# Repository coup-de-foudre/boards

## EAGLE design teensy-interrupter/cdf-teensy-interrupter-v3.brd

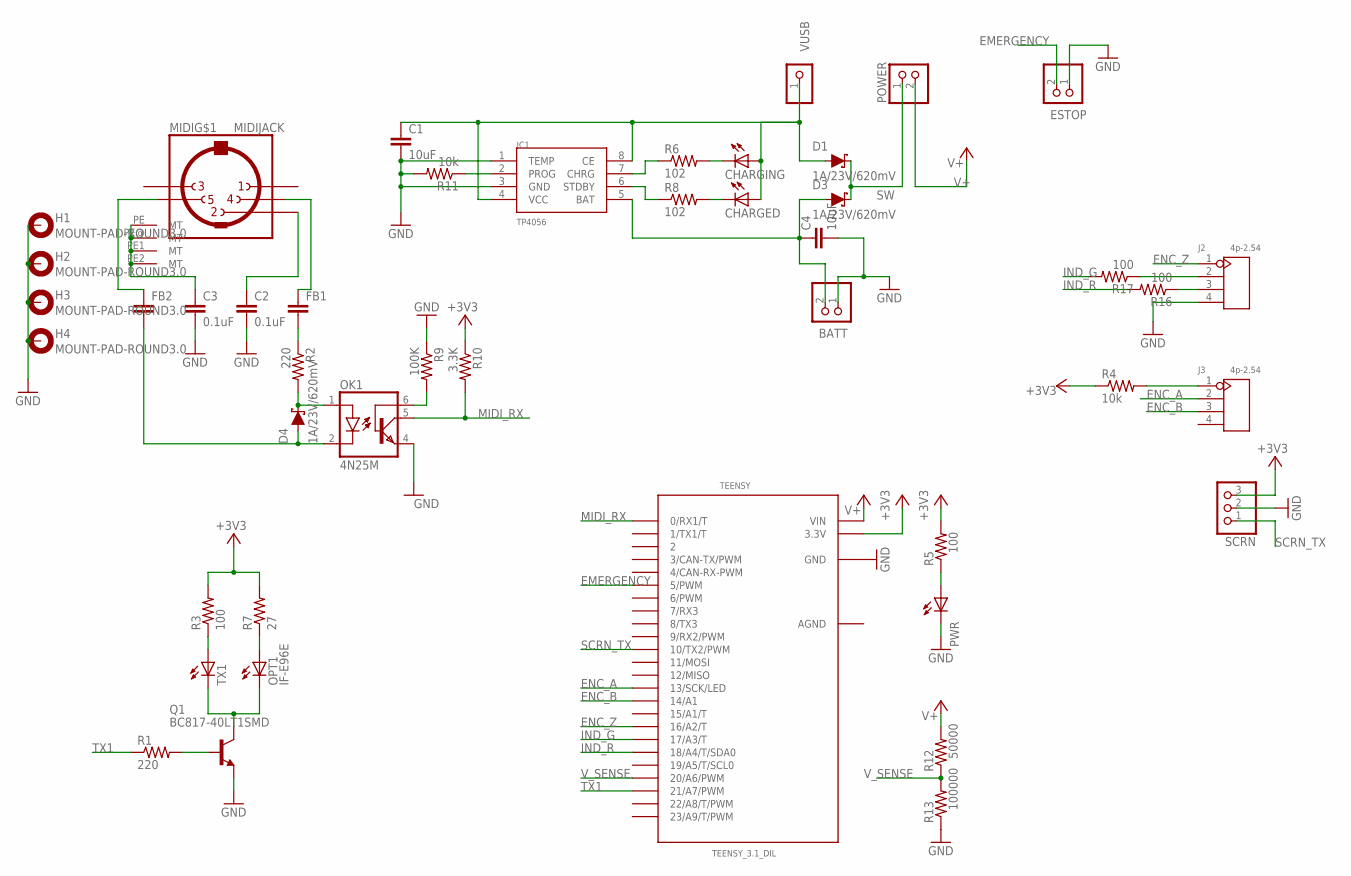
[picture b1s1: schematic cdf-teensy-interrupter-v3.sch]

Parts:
BATT: PINHD-1X2; 1X02
C1, C4: 10uF; C0805
C2, C3: 0.1uF; C0805
CHARGED: LEDCHIP-LED0805; CHIP-LED0805
CHARGING: LEDCHIP-LED0805; CHIP-LED0805
D1, D3, D4: 1A/23V/620mV; SOD-323
ESTOP: PINHD-1X2; 1X02
FB1, FB2: C-EUC0805; C0805
H1, H2, H3, H4: MOUNT-PAD-ROUND3.0; 3,0-PAD
IC1: TP4056; SOP-8
J2, J3: 4p-2.54; H4-2.54
MIDI: MIDIJACK; CP-2350
OK1: 4N25M; DIL06
OPT1: IF-E96E
POWER: PINHD-1X2; 1X02
PWR: LEDCHIP-LED0805; CHIP-LED0805
Q1: BC817-40LT1SMD; SOT23-BEC
R1, R2: 220; R0805
R3, R5, R16, R17: 100; R0805
R4, R11: 10k; R0805
R6, R8: 102; R0805
R7: 27; R0805
R9: 100K; R0805
R10: 3.3K; R0805
R12: 50000; R0805
R13: 100000; R0805
SCRN: PINHD-1X3; 1X03
TEENSY: TEENSY_3.1_DIL; TEENSY3-DIL
TX1: LEDCHIP-LED0805; CHIP-LED0805
VUSB: PINHD-1X1; 1X01

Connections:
+3V3: R3.2, R4.1, R5.2, R7.2, R10.1, SCRN.3, TEENSY.3.3V
AGND: TEENSY.AGND
B+: BATT.2, C4.1, D3.A, IC1.5 (BAT)
EMERGENCY: ESTOP.2, TEENSY.5 (5/PWM)
ENC_A: J3.2, TEENSY.13 (13/SCK/LED)
ENC_B: J3.3, TEENSY.14/A0 (14/A1)
ENC_Z: J2.1, TEENSY.16/A2 (16/A2/T)
GND: BATT.1, C1.2, C2.2, C3.2, C4.2, ESTOP.1, H1.B3,0, H2.B3,0, H3.B3,0, H4.B3,0, IC1.1 (TEMP), IC1.3 (GND), J2.4, OK1.4 (EMI), PWR.C, Q1.E, R9.1, R11.2, R13.1, SCRN.2, TEENSY.GND
IND_G: R17.2, TEENSY.17/A3 (17/A3/T)
IND_R: R16.2, TEENSY.18/A4 (18/A4/T/SDA0)
MIDI_RX: OK1.5 (COL), R10.2, TEENSY.0 (0/RX1/T)
unnamed: FB1.1, MIDI.4
unnamed: D4.C, OK1.1 (A), R2.2
unnamed: D4.A, FB2.2, OK1.2 (C)
unnamed: OK1.6 (BAS), R9.2
unnamed: J3.1, R4.2
unnamed: J2.2, R17.1
unnamed: Q1.B, R1.2
unnamed: OPT1.P$2_ANODE+ (A), R7.1
unnamed: PWR.A, R5.1
unnamed: R3.1, TX1.A
unnamed: OPT1.P$1_CATHODE- (C), Q1.C, TX1.C
unnamed: FB1.2, R2.1
unnamed: C2.1, MIDI.2
unnamed: C3.1, MIDI.PE (MT), MIDI.PE1 (MT), MIDI.PE2 (MT), MIDI.PE@ (MT)
unnamed: FB2.1, MIDI.5
unnamed: IC1.7 (CHRG), R6.1
unnamed: IC1.6 (STDBY), R8.1
unnamed: CHARGED.C, R8.2
unnamed: CHARGING.C, R6.2
unnamed: J2.3, R16.1
unnamed: IC1.2 (PROG), R11.1
SCRN_TX: SCRN.1, TEENSY.10 (10/TX2/PWM)
SW: D1.C, D3.C, POWER.1
TX1: R1.1, TEENSY.21/A7 (21/A7/PWM)
V+: POWER.2, R12.2, TEENSY.VIN
V_SENSE: R12.1, R13.2, TEENSY.20/A6 (20/A6/PWM)
V_USB: C1.1, CHARGED.A, CHARGING.A, D1.A, IC1.4 (VCC), IC1.8 (CE), VUSB.1

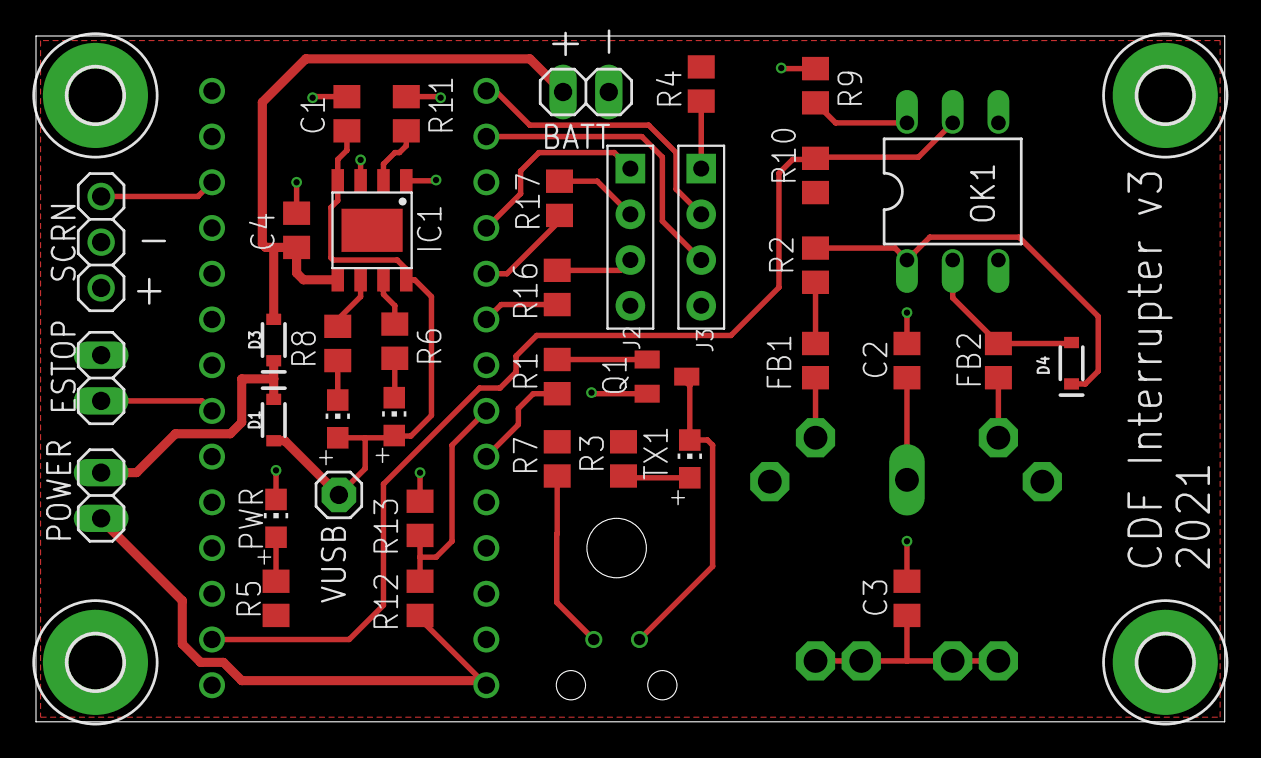
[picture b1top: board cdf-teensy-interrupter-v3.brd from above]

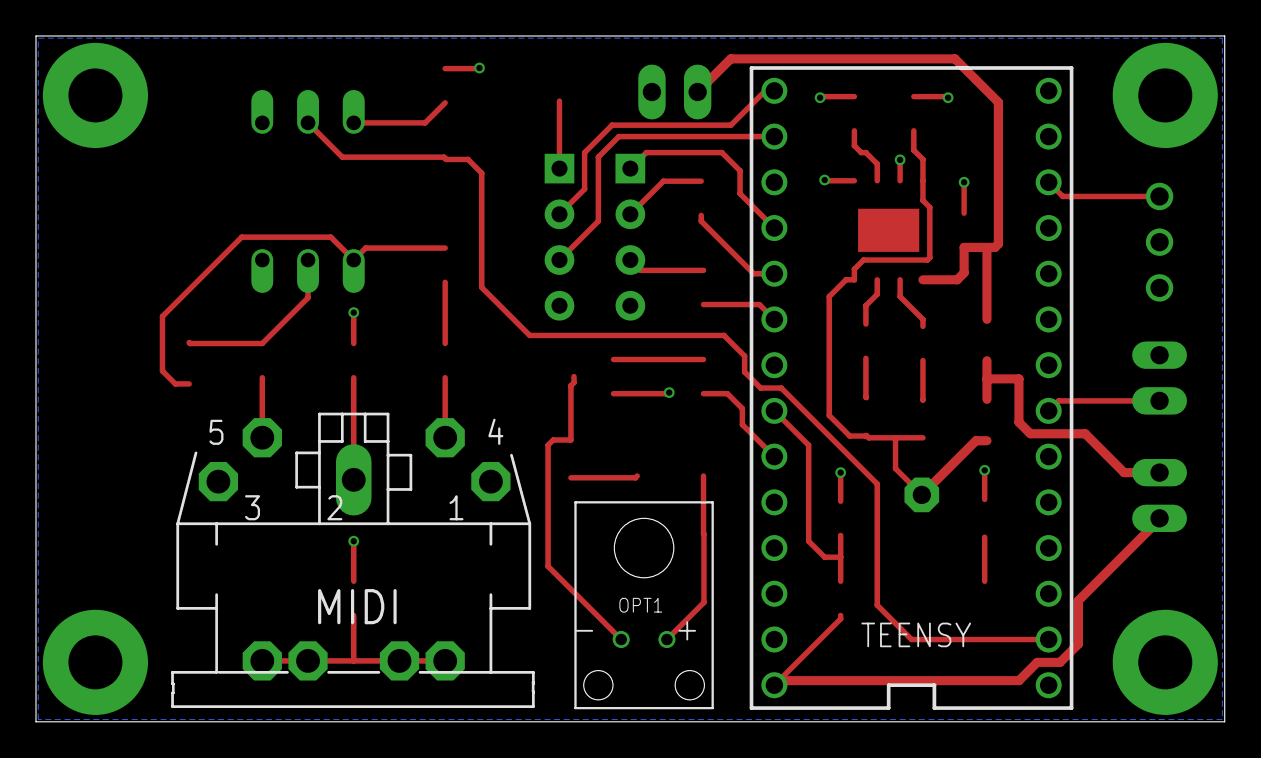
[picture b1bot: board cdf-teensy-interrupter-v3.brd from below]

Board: 2 copper layers, 66.0 x 38.1 mm, 45 parts (3 on the bottom side), 37 nets.

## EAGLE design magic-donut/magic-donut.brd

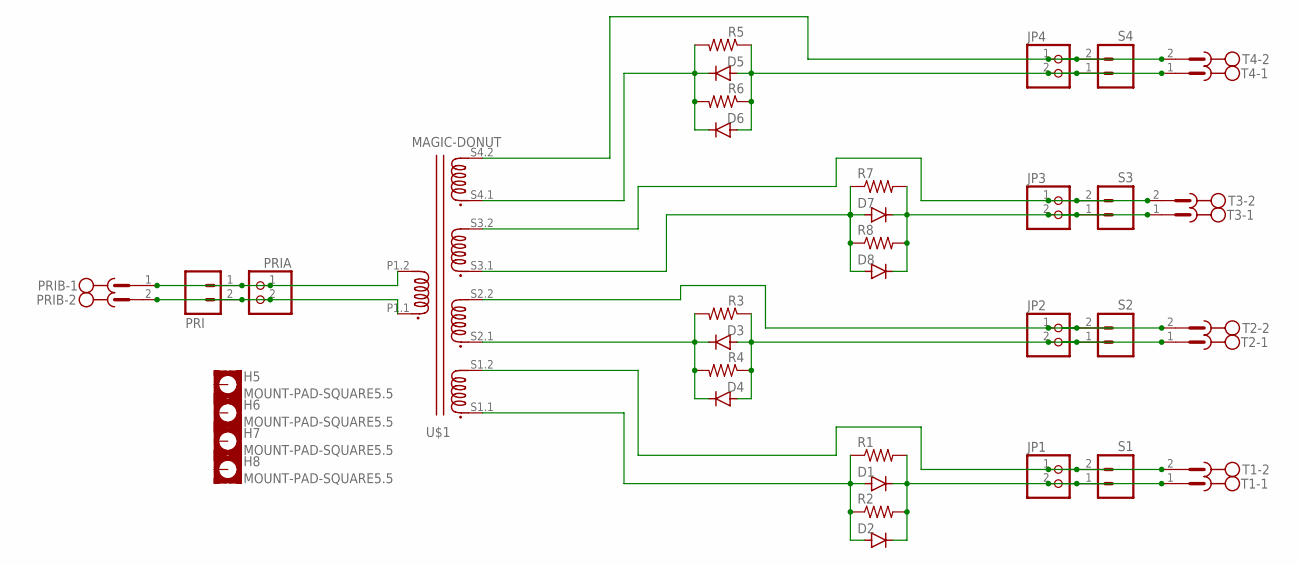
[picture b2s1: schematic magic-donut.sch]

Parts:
D1, D3, D5, D7: DIODE-DO214AA; DO214AA
D2, D4, D6, D8: DIODE-DO201-15; DO201-15
H5, H6, H7, H8: MOUNT-PAD-SQUARE5.5; 5,5-PAD-SQUARE
JP1, JP2, JP3, JP4: PINHD-1X2; 1X02
PRI: M02JST-PTH-2; JST-2-PTH
PRIA: PINHD-1X2; 1X02
PRIB: MSTBV2
R1, R3, R5, R7: R-US_R0805; R0805
R2, R4, R6, R8: R-US_0207/7; 0207/7
S1, S2, S3, S4: M02JST-PTH-2; JST-2-PTH
T1, T2, T3, T4: MSTBV2
U$1: MAGIC-DONUT; TOROID

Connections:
unnamed: D5.C, D6.C, R5.2, R6.2, U$1.S4.1
unnamed: JP3.1, S3.2, T3.2, U$1.S3.2
unnamed: D7.A, D8.A, R7.1, R8.1, U$1.S3.1
unnamed: D3.A, D4.A, JP2.2, R3.1, R4.1, S2.1, T2.1
unnamed: JP4.1, S4.2, T4.2, U$1.S4.2
unnamed: PRI.1, PRIA.1, PRIB.1, U$1.P1.2
unnamed: PRI.2, PRIA.2, PRIB.2, U$1.P1.1
unnamed: D5.A, D6.A, JP4.2, R5.1, R6.1, S4.1, T4.1
unnamed: D7.C, D8.C, JP3.2, R7.2, R8.2, S3.1, T3.1
unnamed: JP2.1, S2.2, T2.2, U$1.S2.2
unnamed: D3.C, D4.C, R3.2, R4.2, U$1.S2.1
unnamed: JP1.1, S1.2, T1.2, U$1.S1.2
unnamed: D1.C, D2.C, JP1.2, R1.2, R2.2, S1.1, T1.1
S1-1: D1.A, D2.A, R1.1, R2.1, U$1.S1.1

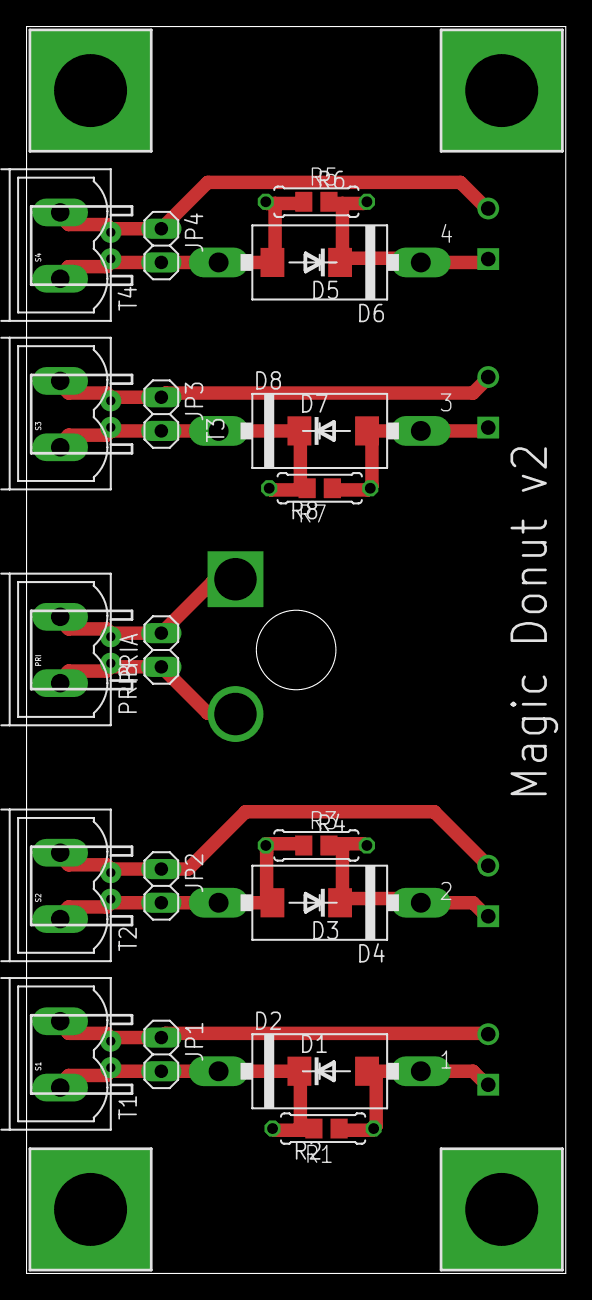
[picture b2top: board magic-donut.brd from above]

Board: 2 copper layers, 40.6 x 94.0 mm, 36 parts (0 on the bottom side), 14 nets.

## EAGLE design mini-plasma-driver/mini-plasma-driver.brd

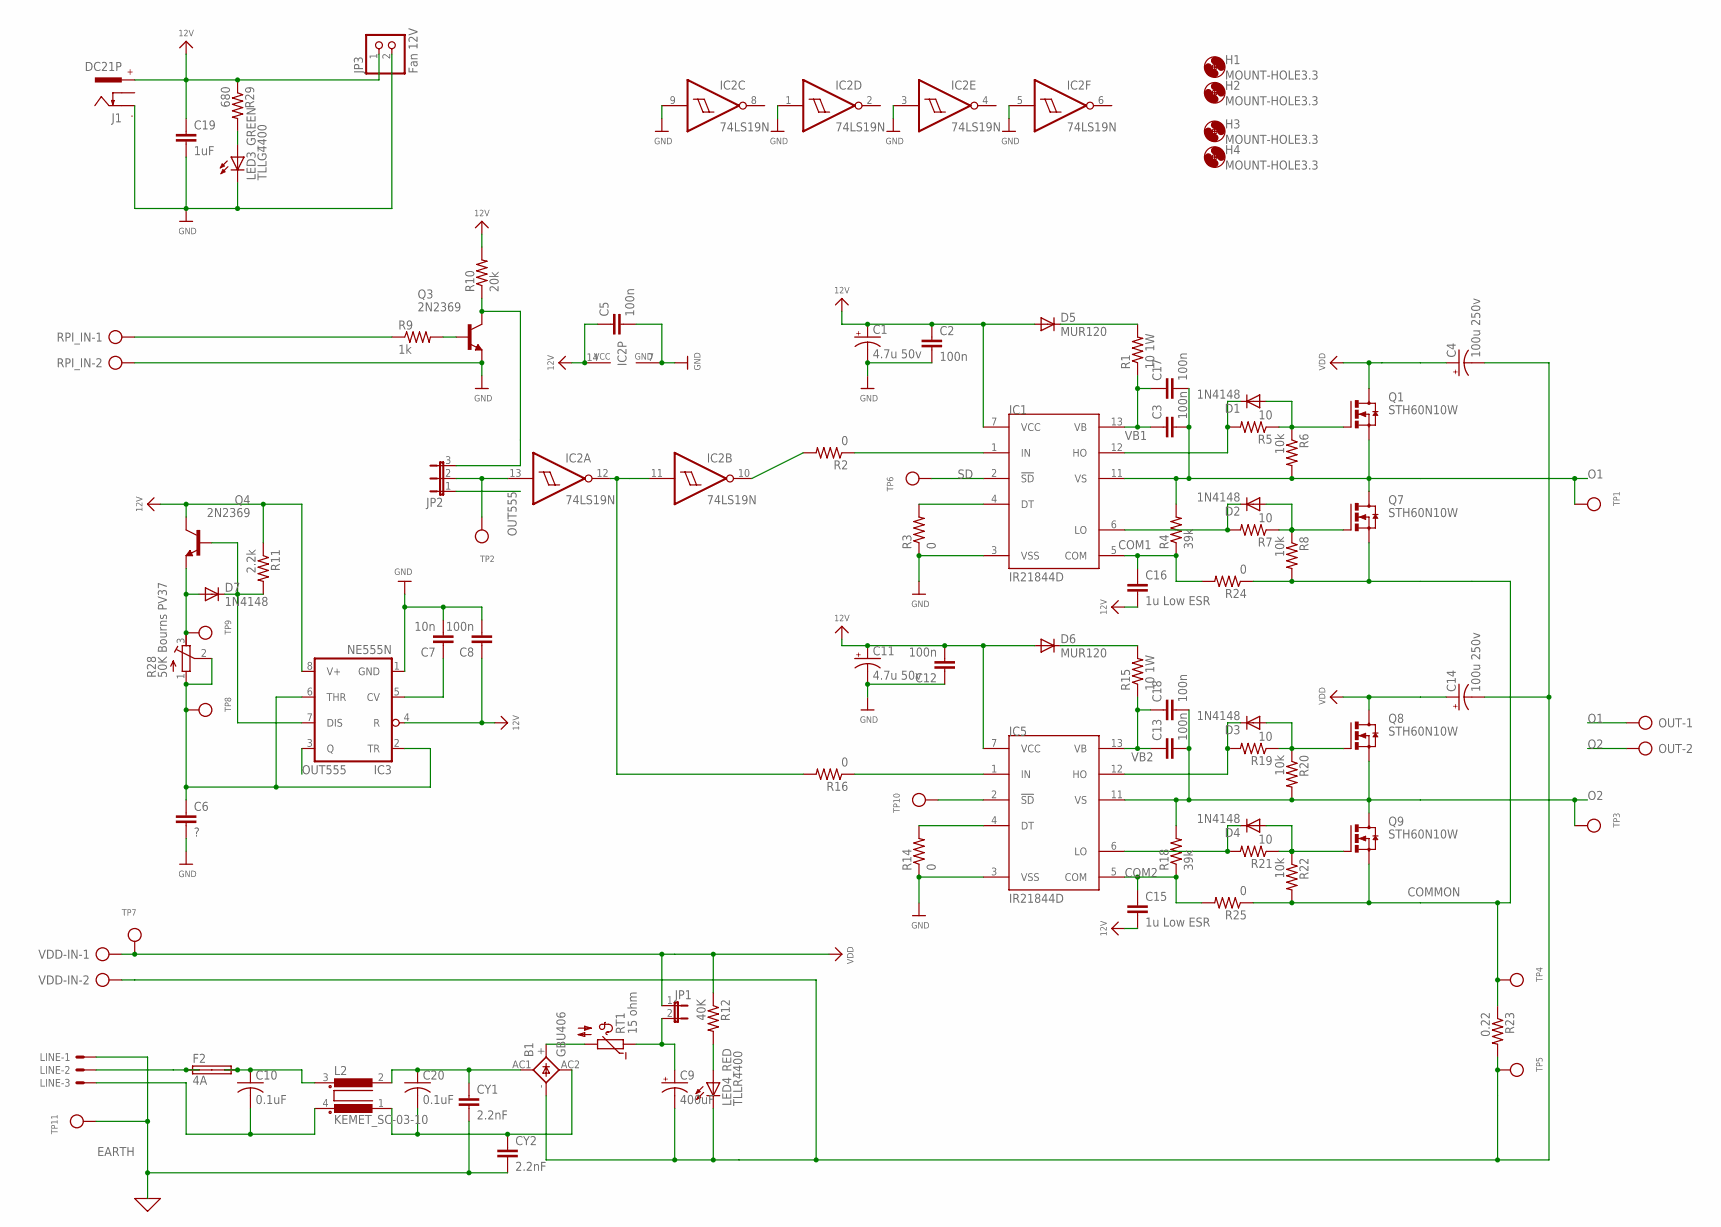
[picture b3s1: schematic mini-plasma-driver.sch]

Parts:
B1: GBU406; 2KBB-R
C1, C11: 4.7u 50v; E2-5
C2, C12: 100n; C025-025X050
C3, C5, C8, C13, C17, C18: 100n; C025-030X050
C4, C14: 100u 250v; E7,5-18
C6: ?; C025-025X050
C7: 10n; C025-030X050
C9: 400uF; E7,5-18
C10, C20: 0.1uF; C150-084X183
C15, C16: 1u Low ESR; C025-025X050
C19: 1uF; C025-025X050
CY1, CY2: 2.2nF; C025-025X050
D1, D2, D3, D4, D7: 1N4148; DO35-10
D5, D6: MUR120; 0309V
F2: 4A; SHK20Q
H1, H2, H3, H4: MOUNT-HOLE3.3; 3,3
IC1, IC5: IR21844D; DIL14
IC2: 74LS19N; DIL14
IC3: NE555N; DIL08
J1: DC21P; CUI-PJ-102AH
JP1: JP1E; JP1
JP2: JP2E; JP2
JP3: Fan 12V; 1X02
L2: KEMET_SC-03-10
LED3_GREEN: TLLG4400; LED3MM
LED4_RED: TLLR4400; LED3MM
LINE: KK-156-3
OUT: AK500/2
Q1, Q7, Q8, Q9: STH60N10W; TO-247AD-V
Q3, Q4: 2N2369; TO18
R1, R15: 10 1W; 0309V
R2, R16, R24, R25: 0; 0207/10
R3, R14: 0; 0309V
R4, R18: 39k; 0207/10
R5, R7, R19, R21: 10; 0207/10
R6, R8, R20, R22: 10k; 0207/10
R9: 1k; 0207/10
R10: 20k; 0207/10
R11: 2.2k; 0207/10
R12: 40K; 0207/10
R23: 0.22; 0617/17
R28: 50K Bourns PV37; RTRIM3296Y
R29: 680; 0207/10
RPI_IN: AK500/2
RT1: 15 ohm; B57164
TP1, TP2, TP3, TP4, TP5, TP6, TP7, TP8, TP9, TP10, TP11: TESTPOINT0.1"; 1X01_ROUND
VDD-IN: AK500/2

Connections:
12V: C1.+, C2.1, C5.1, C8.1, C11.+, C12.2, C15.2, C16.2, C19.1, D5.A, D6.A, IC1.7 (VCC), IC2.14 (VCC), IC3.4 (R), IC3.8 (V+), IC5.7 (VCC), J1.+, JP3.1, Q4.3 (C), R10.2, R11.1, R29.1
COM1: C16.1, IC1.5 (COM), R4.1, R24.2
COM2: C15.1, IC5.5 (COM), R18.1, R25.2
COMMON: Q7.S, Q9.S, R8.2, R22.2, R23.1, R24.1, R25.1, TP4.1
EARTH: CY1.2, CY2.2, LINE.1, TP11.1
GND: C1.-, C2.2, C5.2, C6.2, C7.2, C8.2, C11.-, C12.1, C19.2, IC1.3 (VSS), IC2.1 (I), IC2.3 (I), IC2.5 (I), IC2.7 (GND), IC2.9 (I), IC3.1 (GND), IC5.3 (VSS), J1.-, JP3.2, LED3_GREEN.K (C), Q3.1 (E), R3.1, R14.1, RPI_IN.2
unnamed: D5.C, R1.2
unnamed: C9.+, JP1.2, RT1.1
unnamed: IC1.1 (IN), R2.1
unnamed: IC2.10 (O), R2.2
unnamed: D1.C, IC1.12 (HO), R5.2
unnamed: IC1.4 (DT), R3.2
unnamed: D1.A, Q1.G, R5.1, R6.1
unnamed: D2.C, IC1.6 (LO), R7.2
unnamed: D2.A, Q7.G, R7.1, R8.1
unnamed: R9.1, RPI_IN.1
unnamed: Q3.2 (B), R9.2
unnamed: JP2.3, Q3.3 (C), R10.1
unnamed: IC2.13 (I), JP2.2, TP2.1
unnamed: D7.C, IC3.7 (DIS), Q4.2 (B), R11.2
unnamed: C6.1, IC3.2 (TR), IC3.6 (THR), R28.1 (A), R28.2 (S), TP8.1
unnamed: D7.A, Q4.1 (E), R28.3 (E), TP9.1
unnamed: C7.1, IC3.5 (CV)
unnamed: C10.1, F2.2A, F2.2B, L2.3 (1)
unnamed: F2.1A, F2.1B, LINE.2
unnamed: B1.AC1, C20.1, CY1.1, L2.2
unnamed: D6.C, R15.2
unnamed: C10.2, L2.4 (3), LINE.3
unnamed: IC5.1 (IN), R16.1
unnamed: B1.+, RT1.2
unnamed: IC5.4 (DT), R14.2
unnamed: D3.C, IC5.12 (HO), R19.2
unnamed: D3.A, Q8.G, R19.1, R20.1
unnamed: D4.C, IC5.6 (LO), R21.2
unnamed: D4.A, Q9.G, R21.1, R22.1
unnamed: B1.AC2, C20.2, CY2.1, L2.1 (4)
unnamed: LED4_RED.A, R12.2
unnamed: IC5.2 (!SD), TP10.1
unnamed: LED3_GREEN.A, R29.2
unnamed: IC2.11 (I), IC2.12 (O), R16.2
O1: C3.2, C17.2, IC1.11 (VS), OUT.1, Q1.S, Q7.D, R4.2, R6.2, TP1.1
O2: C13.2, C18.2, IC5.11 (VS), OUT.2, Q8.S, Q9.D, R18.2, R20.2, TP3.1
OUT555: IC3.3 (Q), JP2.1
SD: IC1.2 (!SD), TP6.1
VB1: C3.1, C17.1, IC1.13 (VB), R1.1
VB2: C13.1, C18.1, IC5.13 (VB), R15.1
VDD+: C4.+, C14.+, JP1.1, Q1.D, Q8.D, R12.1, TP7.1, VDD-IN.1
VDD-: B1.-, C4.-, C9.-, C14.-, LED4_RED.K (C), R23.2, TP5.1, VDD-IN.2

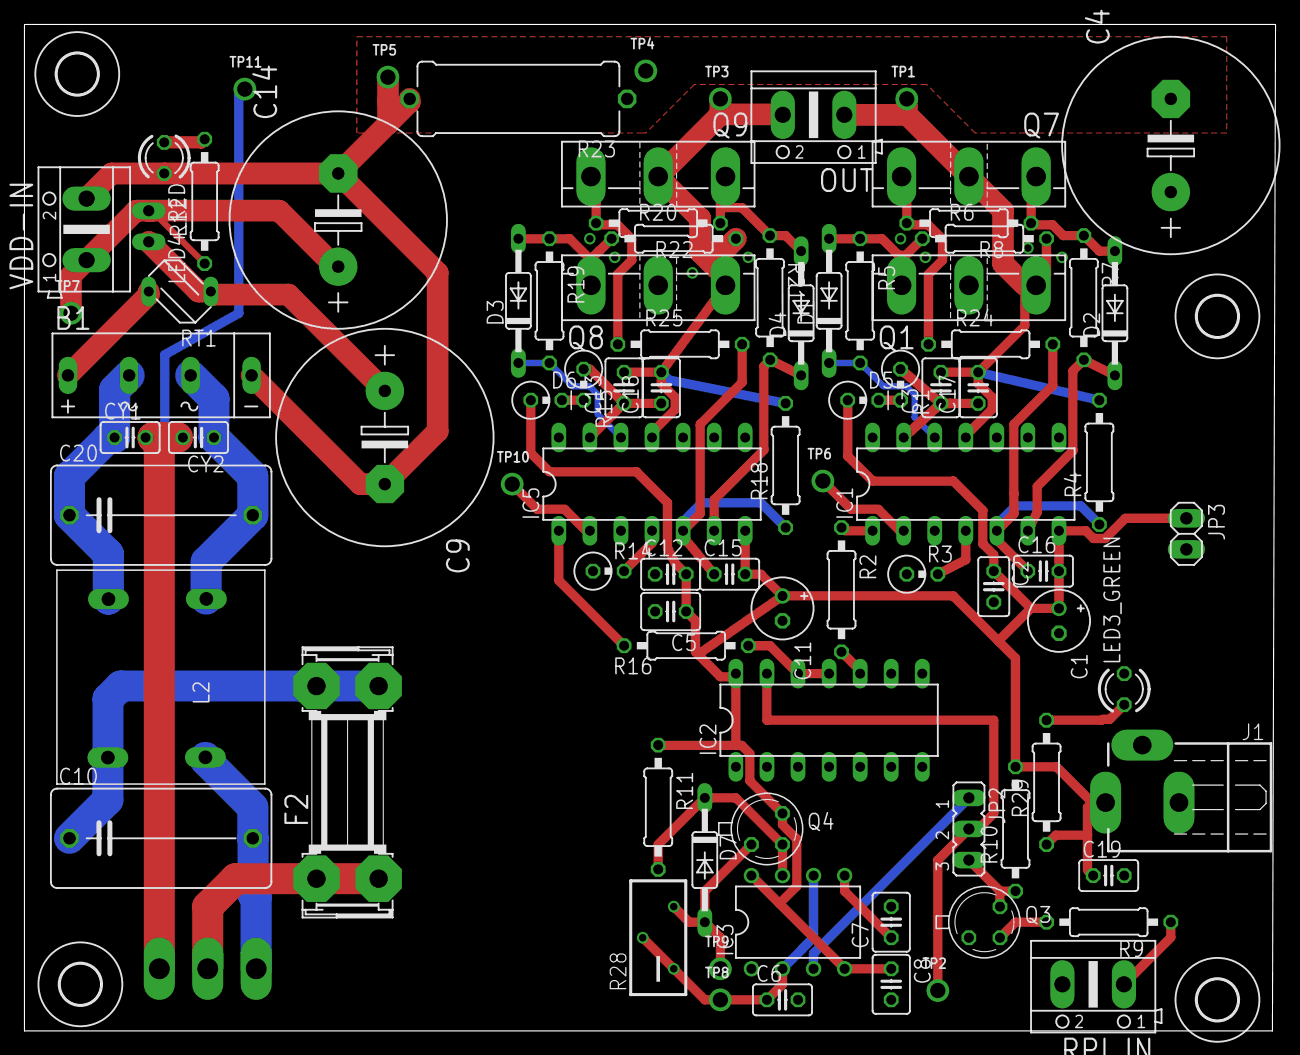
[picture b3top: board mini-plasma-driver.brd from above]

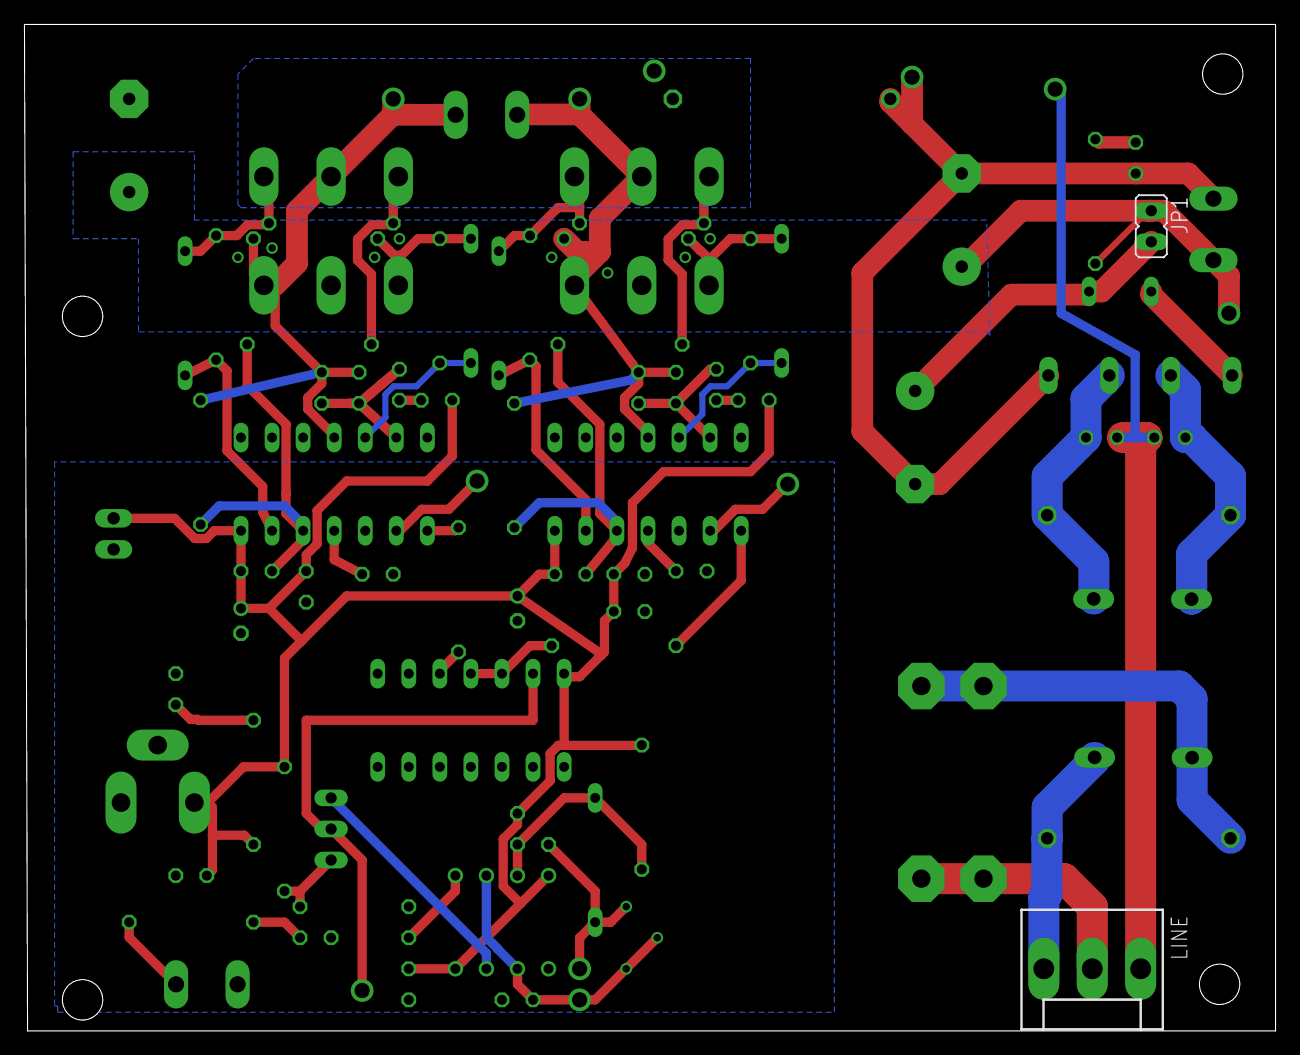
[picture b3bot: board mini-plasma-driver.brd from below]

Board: 2 copper layers, 102.3 x 82.3 mm, 93 parts (2 on the bottom side), 48 nets.

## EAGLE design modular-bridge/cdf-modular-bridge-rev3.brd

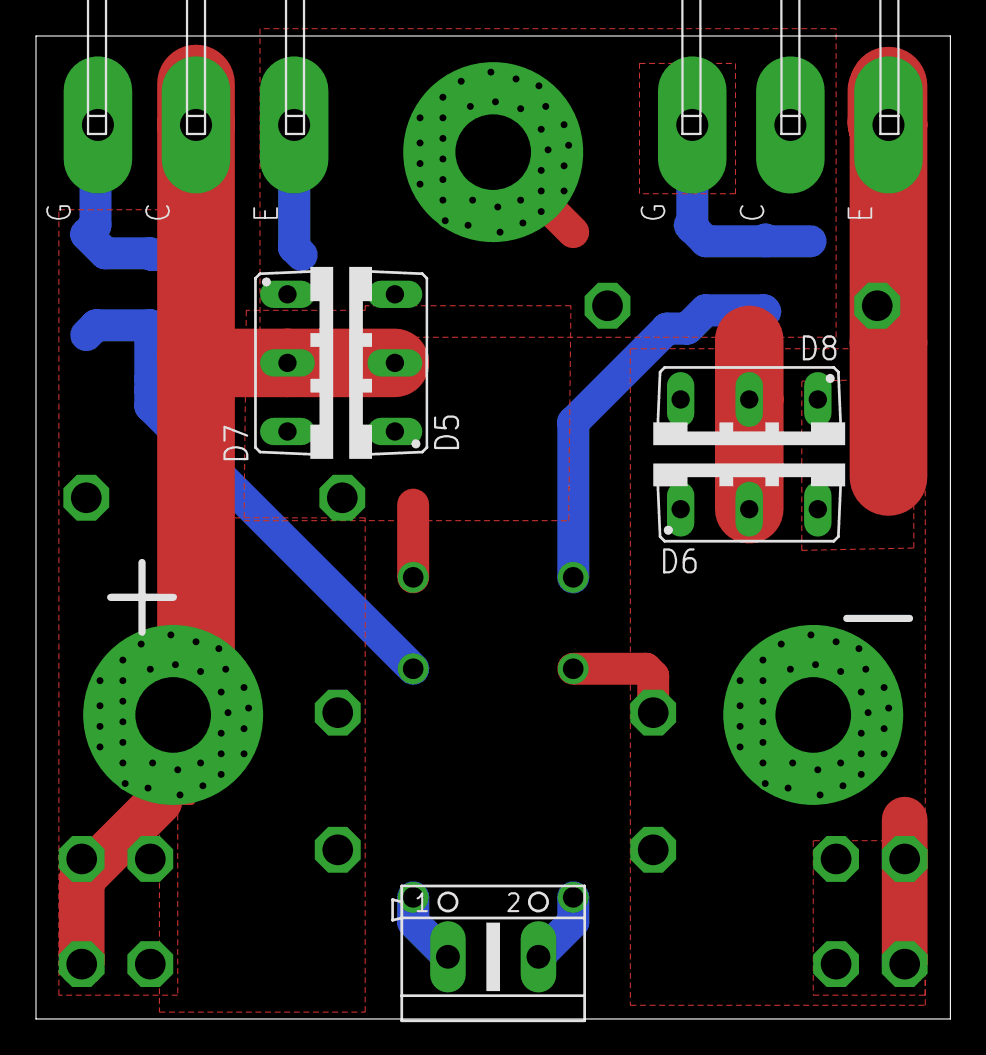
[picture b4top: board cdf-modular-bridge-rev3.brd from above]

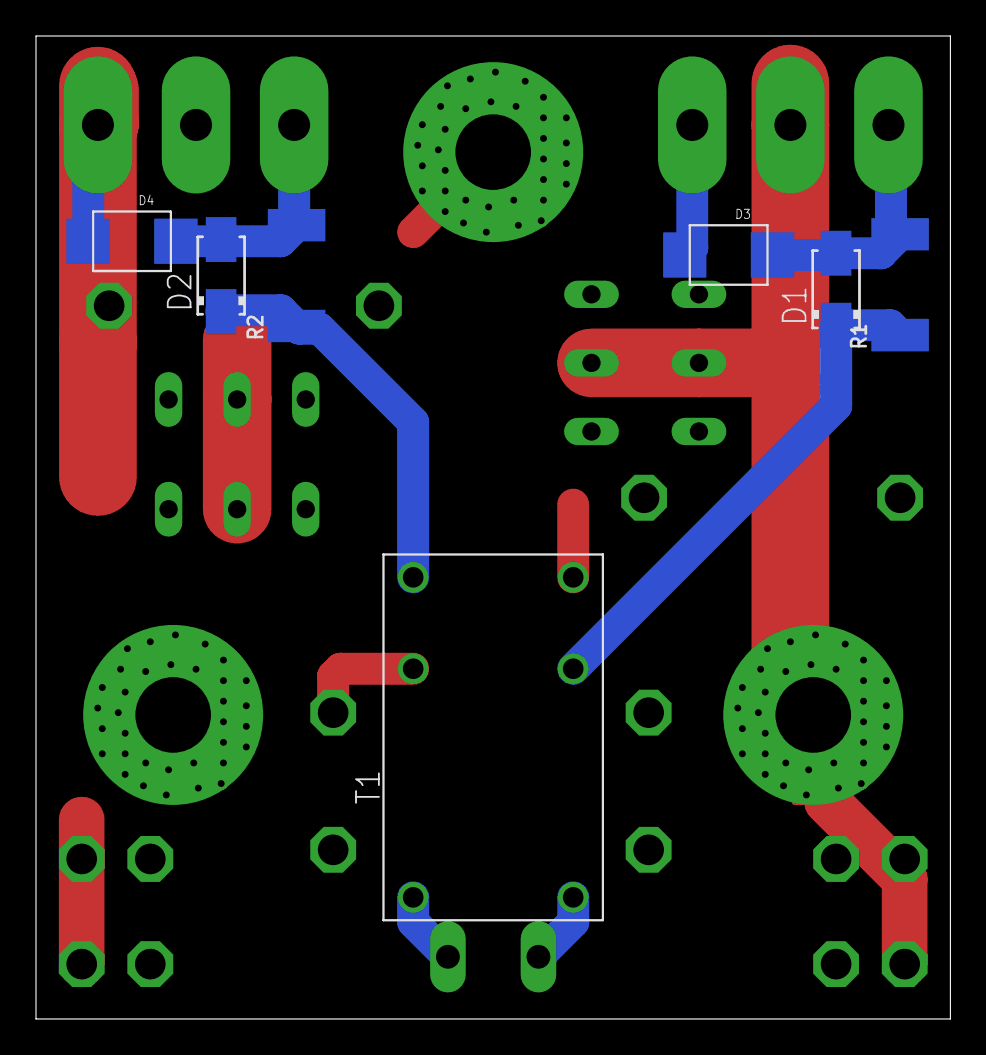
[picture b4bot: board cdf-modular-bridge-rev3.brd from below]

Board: 2 copper layers, 50.8 x 54.6 mm, 33 parts (7 on the bottom side), 9 nets.

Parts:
D1, D2: FM5819-W; DO214AC
D3, D4: TPSMB30CA; TPSMB15CA
D5, D6, D7, D8: FMN-2206S2; TO220-CDF-SPACED-LEGS
DC+: BIG-ASS-HOLE
DC-: BIG-ASS-HOLE
OUT: BIG-ASS-HOLE
Q1, Q2: Ixgh48n60a3; IXGH40N60A
R1, R2: 15 (352115RFT); 2512
T1: PULSE-P0584NL
TP1, TP2, TP3, TP4, TP5, TP6, TP7, TP8, TP9, TP10, TP11, TP12, TP13, TP14, TP15, TP16: PTR1PAD1-17; P1-17
X1: AK500/2

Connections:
DC+: D5.C, D7.C, DC+.X, DC+.X@1, DC+.X@2, DC+.X@3, DC+.X@4, DC+.X@5, DC+.X@6, DC+.X@7, DC+.X@8, DC+.X@9, DC+.X@10, DC+.X@11, DC+.X@12, DC+.X@13, DC+.X@14, DC+.X@15, DC+.X@16, DC+.X@17, DC+.X@18, DC+.X@19, DC+.X@20, DC+.X@21, DC+.X@22, DC+.X@23, DC+.X@24, DC+.X@25, DC+.X@26, DC+.X@27, DC+.X@28, DC+.X@29, DC+.X@30, DC+.X@31, DC+.X@32, DC+.X@34, DC+.X@120, Q1.C, TP1.TP, TP4.TP, TP5.TP, TP6.TP, TP9.TP, TP10.TP, TP11.TP
DC-: D4.P$2, D6.A1, D6.A2, D8.A1, D8.A2, DC-.X, DC-.X@1, DC-.X@2, DC-.X@3, DC-.X@4, DC-.X@5, DC-.X@6, DC-.X@7, DC-.X@8, DC-.X@9, DC-.X@10, DC-.X@11, DC-.X@12, DC-.X@13, DC-.X@14, DC-.X@15, DC-.X@16, DC-.X@17, DC-.X@18, DC-.X@19, DC-.X@20, DC-.X@21, DC-.X@22, DC-.X@23, DC-.X@24, DC-.X@25, DC-.X@26, DC-.X@27, DC-.X@28, DC-.X@29, DC-.X@30, DC-.X@31, DC-.X@32, DC-.X@34, DC-.X@120, Q2.E, T1.8, TP2.TP, TP3.TP, TP7.TP, TP8.TP, TP14.TP, TP15.TP, TP16.TP
unnamed: T1.10, X1.2
unnamed: T1.1, X1.1
unnamed: D1.A, D3.P$1, Q1.G, R1.2
unnamed: D2.A, D4.P$1, Q2.G, R2.2
unnamed: D2.C, R2.1, T1.7
unnamed: D1.C, R1.1, T1.3
OUT: D3.P$2, D5.A1, D5.A2, D6.C, D7.A1, D7.A2, D8.C, OUT.X, OUT.X@1, OUT.X@2, OUT.X@3, OUT.X@4, OUT.X@5, OUT.X@6, OUT.X@7, OUT.X@8, OUT.X@9, OUT.X@10, OUT.X@11, OUT.X@12, OUT.X@13, OUT.X@14, OUT.X@15, OUT.X@16, OUT.X@17, OUT.X@18, OUT.X@19, OUT.X@20, OUT.X@21, OUT.X@22, OUT.X@23, OUT.X@24, OUT.X@25, OUT.X@26, OUT.X@27, OUT.X@28, OUT.X@29, OUT.X@30, OUT.X@31, OUT.X@32, OUT.X@34, OUT.X@120, Q1.E, Q2.C, T1.4, TP12.TP, TP13.TP

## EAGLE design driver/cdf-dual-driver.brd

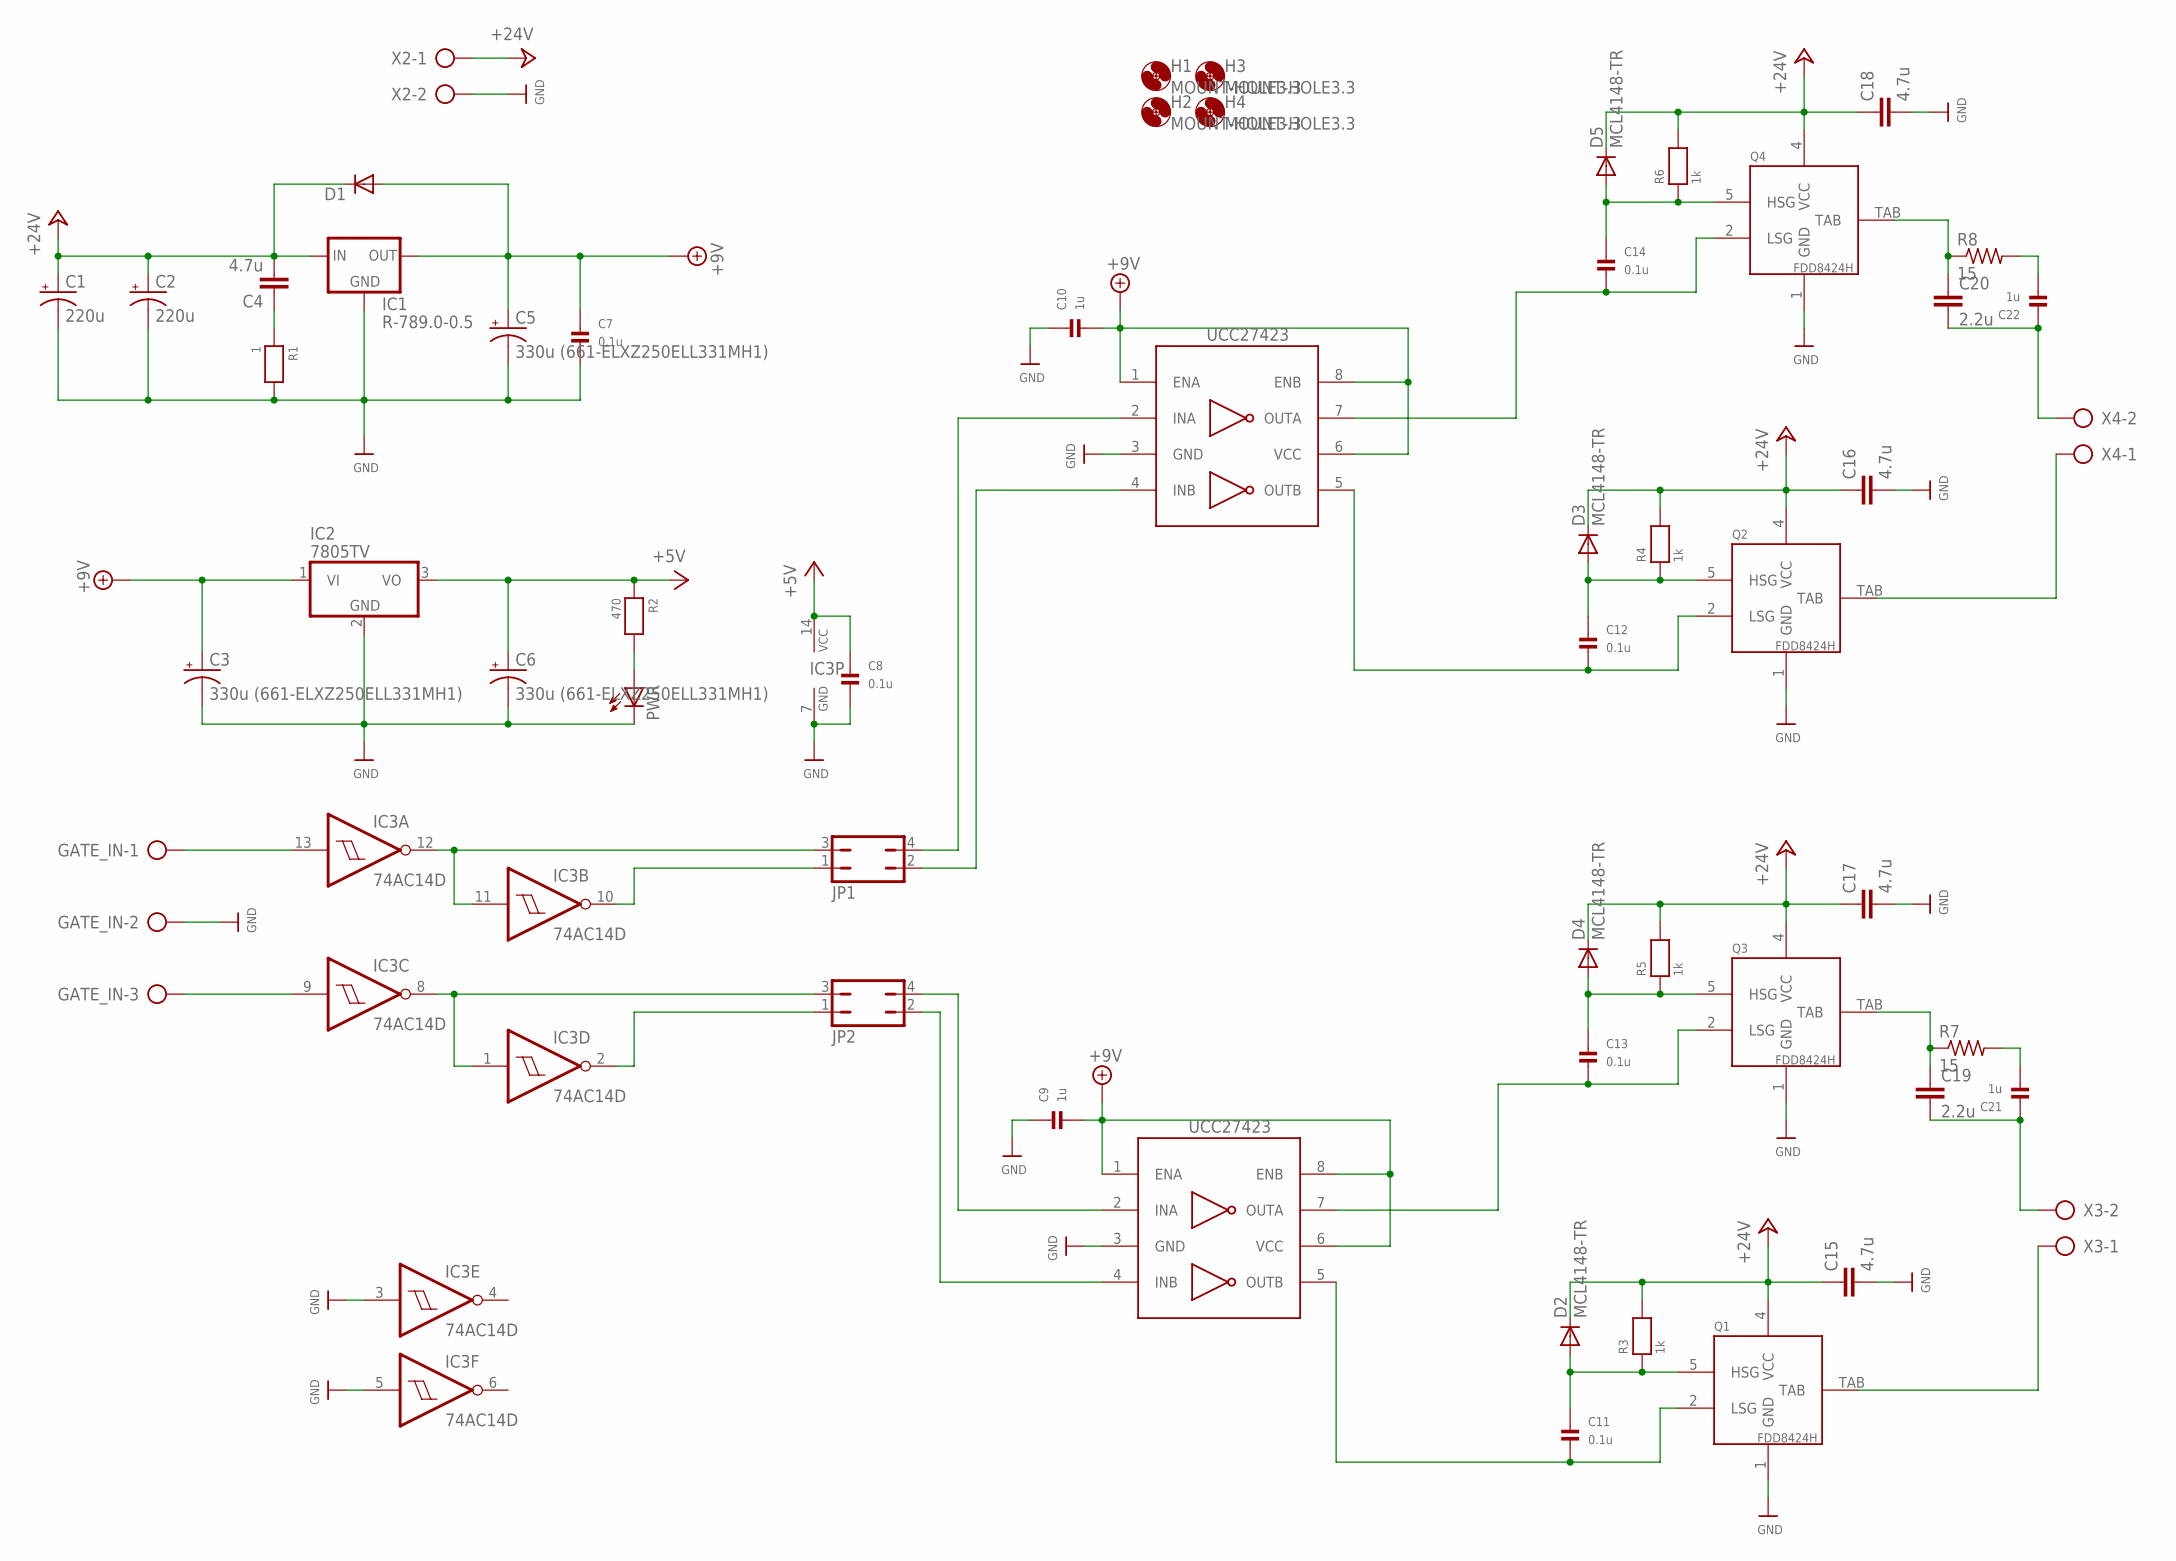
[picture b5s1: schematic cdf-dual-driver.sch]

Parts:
C1, C2: 220u; E3,5-8
C3, C5, C6: 330u (661-ELXZ250ELL331MH1); E3,5-8
C4, C15, C16, C17, C18: 4.7u; C1210
C7, C8, C11, C12, C13, C14: 0.1u; 0805
C9, C10, C21, C22: 1u; 1206
C19, C20: 2.2u; C1210
D1: DIODE-SOD123; SOD123
D2, D3, D4, D5: MCL4148-TR; MICROMELF-W
GATE_IN: AK500/3
H1, H2, H3, H4: MOUNT-HOLE3.3; 3,3
IC1: R-789.0-0.5; SIP3
IC2: 7805TV; TO220V
IC3: 74AC14D; SO14
IC4, IC5: UCC27423; SOIC8
JP1, JP2: JP2Q
PWR: LED5MM
Q1, Q2, Q3, Q4: FDD8424H; TO252-4
R1: 1; 0805
R2: 470; 0805
R3, R4, R5, R6: 1k; 0805
R7, R8: 15; R1210
X2, X3, X4: AK500/2

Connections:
+5V: C6.+, C8.1, IC2.3 (VO), IC3.14 (VCC), R2.1
+9V: C3.+, C5.+, C7.1, C9.2, C10.2, D1.A, IC1.3 (OUT), IC2.1 (VI), IC4.1 (ENA), IC4.6 (VCC), IC4.8 (ENB), IC5.1 (ENA), IC5.6 (VCC), IC5.8 (ENB)
+24V: C1.+, C2.+, C4.2, C15.1, C16.1, C17.1, C18.1, D1.C, D2.C, D3.C, D4.C, D5.C, IC1.1 (IN), Q1.4 (VCC), Q2.4 (VCC), Q3.4 (VCC), Q4.4 (VCC), R3.2, R4.2, R5.2, R6.2, X2.1
GND: C1.-, C2.-, C3.-, C5.-, C6.-, C7.2, C8.2, C9.1, C10.1, C15.2, C16.2, C17.2, C18.2, GATE_IN.2, IC1.2 (GND), IC2.2 (GND), IC3.3 (I), IC3.5 (I), IC3.7 (GND), IC4.3 (GND), IC5.3 (GND), PWR.K (C), Q1.1 (GND), Q2.1 (GND), Q3.1 (GND), Q4.1 (GND), R1.2, X2.2
unnamed: C13.2, IC4.7 (OUTA), Q3.2 (LSG)
unnamed: C13.1, D4.A, Q3.5 (HSG), R5.1
unnamed: C14.2, IC5.7 (OUTA), Q4.2 (LSG)
unnamed: C14.1, D5.A, Q4.5 (HSG), R6.1
unnamed: C20.1, Q4.TAB, R8.1
unnamed: C22.2, R8.2
unnamed: C20.2, C22.1, X4.2
unnamed: C12.2, IC5.5 (OUTB), Q2.2 (LSG)
unnamed: C12.1, D3.A, Q2.5 (HSG), R4.1
unnamed: Q2.TAB, X4.1
unnamed: C4.1, R1.1
unnamed: C19.1, Q3.TAB, R7.1
unnamed: C21.2, R7.2
unnamed: C19.2, C21.1, X3.2
unnamed: C11.2, IC4.5 (OUTB), Q1.2 (LSG)
unnamed: C11.1, D2.A, Q1.5 (HSG), R3.1
unnamed: Q1.TAB, X3.1
unnamed: PWR.A, R2.2
unnamed: IC5.2 (INA), JP1.4
unnamed: IC5.4 (INB), JP1.2
unnamed: IC4.2 (INA), JP2.4
unnamed: IC4.4 (INB), JP2.2
unnamed: IC3.11 (I), IC3.12 (O), JP1.3
unnamed: GATE_IN.1, IC3.13 (I)
unnamed: GATE_IN.3, IC3.9 (I)
unnamed: IC3.10 (O), JP1.1
unnamed: IC3.1 (I), IC3.8 (O), JP2.3
unnamed: IC3.2 (O), JP2.1

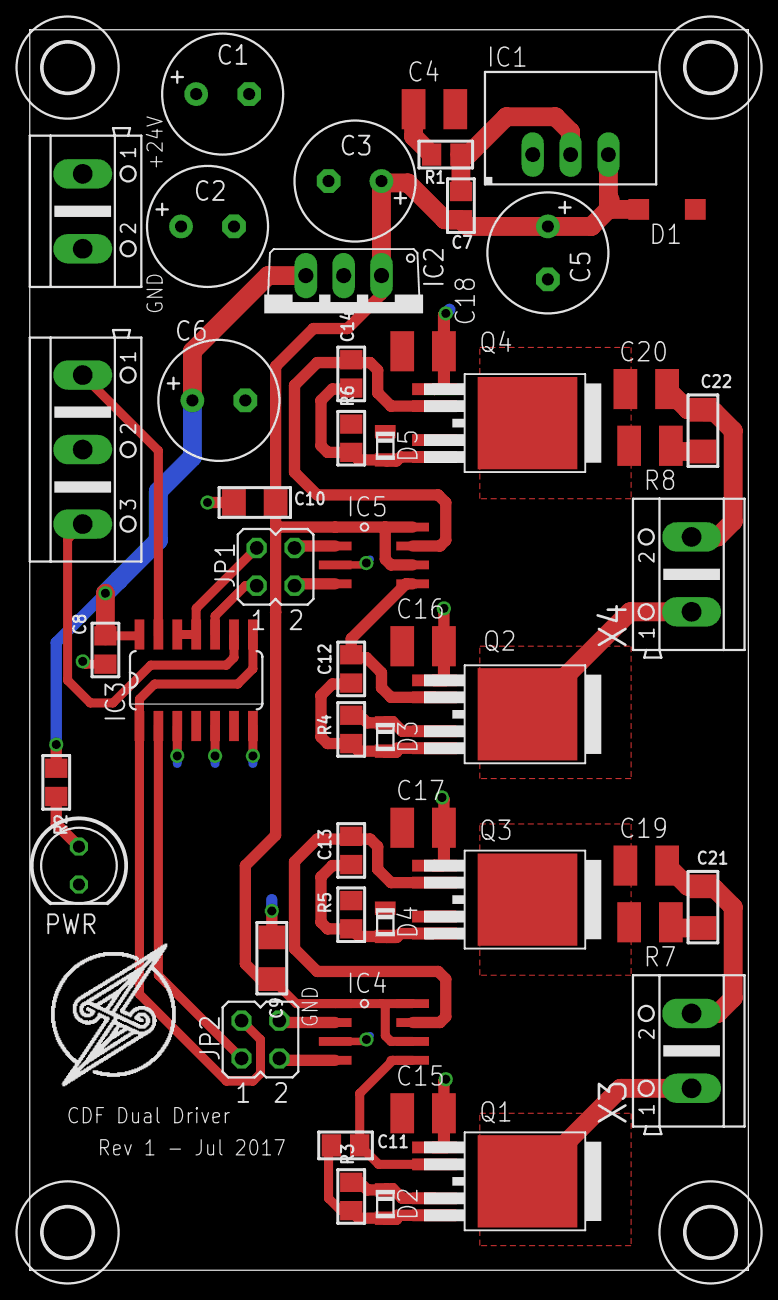
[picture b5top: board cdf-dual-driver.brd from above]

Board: 2 copper layers, 48.3 x 83.3 mm, 55 parts (0 on the bottom side), 32 nets.

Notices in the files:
parts and their libraries:
microbuilder: This work is placed in the public domain, and may be freely used for commercial and non-commercial work with the following conditions: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
r-78xx_10: (c) 2015 Samuel Lourenço
